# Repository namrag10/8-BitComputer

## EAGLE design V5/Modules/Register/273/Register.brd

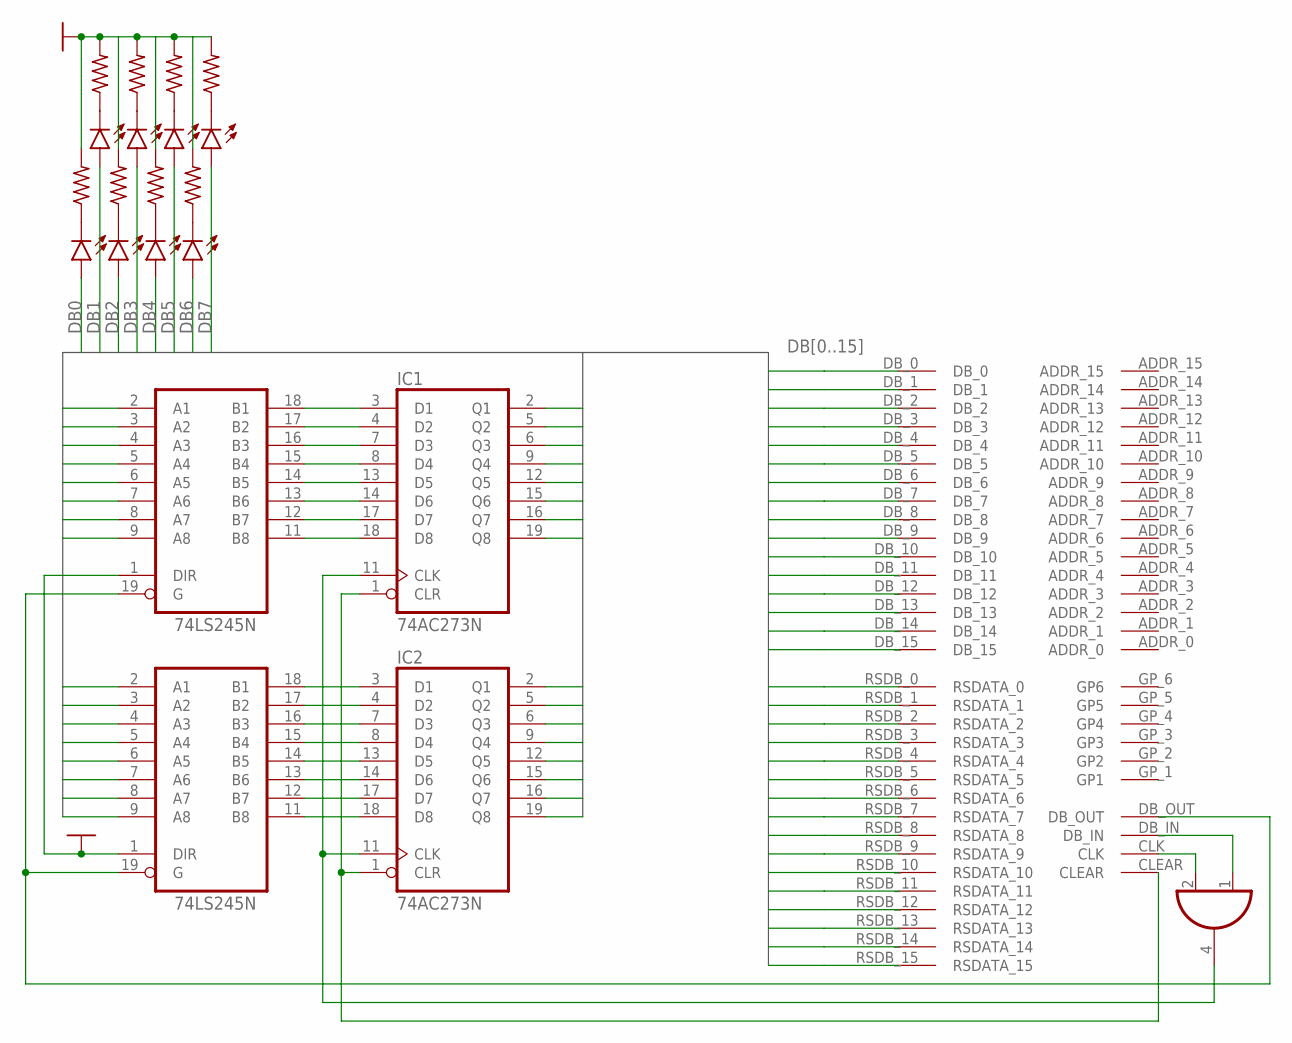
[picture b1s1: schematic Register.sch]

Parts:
IC1, IC2: 74AC273N; DIL20
IC4: 74AHC1G08DCK; SC70-5
LED_A_REG_1, LED_A_REG_2, LED_A_REG_3, LED_A_REG_4, LED_A_REG_5, LED_A_REG_6, LED_A_REG_7, LED_A_REG_8: LED; LED5MM
OUTPUT_BUFFER_REG_A, OUTPUT_BUFFER_REG_A1: 74LS245N; DIL20
R1, R2, R3, R4, R5, R6, R7, R8: ~220; 0204/7
U$1: BACKPLATE_INTERFACE; BACK_INTERFACE-FOOT

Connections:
DB0: IC1.2 (Q1), LED_A_REG_1.A, OUTPUT_BUFFER_REG_A1.2 (A1), U$1.DB_0, U$1.RSDB_0 (RSDATA_0)
DB1: IC1.5 (Q2), LED_A_REG_2.A, OUTPUT_BUFFER_REG_A1.3 (A2), U$1.DB_1, U$1.RSDB_1 (RSDATA_1)
DB2: IC1.6 (Q3), LED_A_REG_3.A, OUTPUT_BUFFER_REG_A1.4 (A3), U$1.DB_2, U$1.RSDB_2 (RSDATA_2)
DB3: IC1.9 (Q4), LED_A_REG_4.A, OUTPUT_BUFFER_REG_A1.5 (A4), U$1.DB_3, U$1.RSDB_3 (RSDATA_3)
DB4: IC1.12 (Q5), LED_A_REG_5.A, OUTPUT_BUFFER_REG_A1.6 (A5), U$1.DB_4, U$1.RSDB_4 (RSDATA_4)
DB5: IC1.15 (Q6), LED_A_REG_6.A, OUTPUT_BUFFER_REG_A1.7 (A6), U$1.DB_5, U$1.RSDB_5 (RSDATA_5)
DB6: IC1.16 (Q7), LED_A_REG_7.A, OUTPUT_BUFFER_REG_A1.8 (A7), U$1.DB_6, U$1.RSDB_6 (RSDATA_6)
DB7: IC1.19 (Q8), LED_A_REG_8.A, OUTPUT_BUFFER_REG_A1.9 (A8), U$1.DB_7, U$1.RSDB_7 (RSDATA_7)
DB8: IC2.2 (Q1), OUTPUT_BUFFER_REG_A.2 (A1), U$1.DB_8, U$1.RSDB_8 (RSDATA_8)
DB9: IC2.5 (Q2), OUTPUT_BUFFER_REG_A.3 (A2), U$1.DB_9, U$1.RSDB_9 (RSDATA_9)
DB10: IC2.6 (Q3), OUTPUT_BUFFER_REG_A.4 (A3), U$1.DB_10, U$1.RSDB_10 (RSDATA_10)
DB11: IC2.9 (Q4), OUTPUT_BUFFER_REG_A.5 (A4), U$1.DB_11, U$1.RSDB_11 (RSDATA_11)
DB12: IC2.12 (Q5), OUTPUT_BUFFER_REG_A.6 (A5), U$1.DB_12, U$1.RSDB_12 (RSDATA_12)
DB13: IC2.15 (Q6), OUTPUT_BUFFER_REG_A.7 (A6), U$1.DB_13, U$1.RSDB_13 (RSDATA_13)
DB14: IC2.16 (Q7), OUTPUT_BUFFER_REG_A.8 (A7), U$1.DB_14, U$1.RSDB_14 (RSDATA_14)
DB15: IC2.19 (Q8), OUTPUT_BUFFER_REG_A.9 (A8), U$1.DB_15, U$1.RSDB_15 (RSDATA_15)
GND: IC1.10 (GND), IC2.10 (GND), IC4.3 (GND), OUTPUT_BUFFER_REG_A.1 (DIR), OUTPUT_BUFFER_REG_A.10 (GND), OUTPUT_BUFFER_REG_A1.1 (DIR), OUTPUT_BUFFER_REG_A1.10 (GND), R1.2, R2.2, R4.2, R6.2, R8.2, U$1.GND, U$1.GND2 (GND)
unnamed: OUTPUT_BUFFER_REG_A.19 (G), OUTPUT_BUFFER_REG_A1.19 (G), U$1.DB_OUT
unnamed: LED_A_REG_1.K (C), R1.1
unnamed: IC1.18 (D8), OUTPUT_BUFFER_REG_A1.11 (B8)
unnamed: IC1.17 (D7), OUTPUT_BUFFER_REG_A1.12 (B7)
unnamed: IC1.14 (D6), OUTPUT_BUFFER_REG_A1.13 (B6)
unnamed: IC1.13 (D5), OUTPUT_BUFFER_REG_A1.14 (B5)
unnamed: IC1.8 (D4), OUTPUT_BUFFER_REG_A1.15 (B4)
unnamed: IC1.7 (D3), OUTPUT_BUFFER_REG_A1.16 (B3)
unnamed: IC1.4 (D2), OUTPUT_BUFFER_REG_A1.17 (B2)
unnamed: IC1.3 (D1), OUTPUT_BUFFER_REG_A1.18 (B1)
unnamed: IC2.18 (D8), OUTPUT_BUFFER_REG_A.11 (B8)
unnamed: IC2.17 (D7), OUTPUT_BUFFER_REG_A.12 (B7)
unnamed: IC2.14 (D6), OUTPUT_BUFFER_REG_A.13 (B6)
unnamed: IC2.13 (D5), OUTPUT_BUFFER_REG_A.14 (B5)
unnamed: IC2.8 (D4), OUTPUT_BUFFER_REG_A.15 (B4)
unnamed: IC2.7 (D3), OUTPUT_BUFFER_REG_A.16 (B3)
unnamed: IC2.4 (D2), OUTPUT_BUFFER_REG_A.17 (B2)
unnamed: IC2.3 (D1), OUTPUT_BUFFER_REG_A.18 (B1)
unnamed: IC4.2 (I1), U$1.CLK
unnamed: IC1.1 (CLR), IC2.1 (CLR), U$1.CLEAR
unnamed: IC1.11 (CLK), IC2.11 (CLK), IC4.4 (O)
unnamed: IC4.1 (I0), U$1.DB_IN
unnamed: LED_A_REG_2.K (C), R2.1
unnamed: LED_A_REG_3.K (C), R3.1
unnamed: LED_A_REG_4.K (C), R4.1
unnamed: LED_A_REG_5.K (C), R5.1
unnamed: LED_A_REG_6.K (C), R6.1
unnamed: LED_A_REG_7.K (C), R7.1
unnamed: LED_A_REG_8.K (C), R8.1
VCC: IC1.20 (VCC), IC2.20 (VCC), IC4.5 (VCC), OUTPUT_BUFFER_REG_A.20 (VCC), OUTPUT_BUFFER_REG_A1.20 (VCC), U$1.VCC, U$1.VCC2 (VCC)

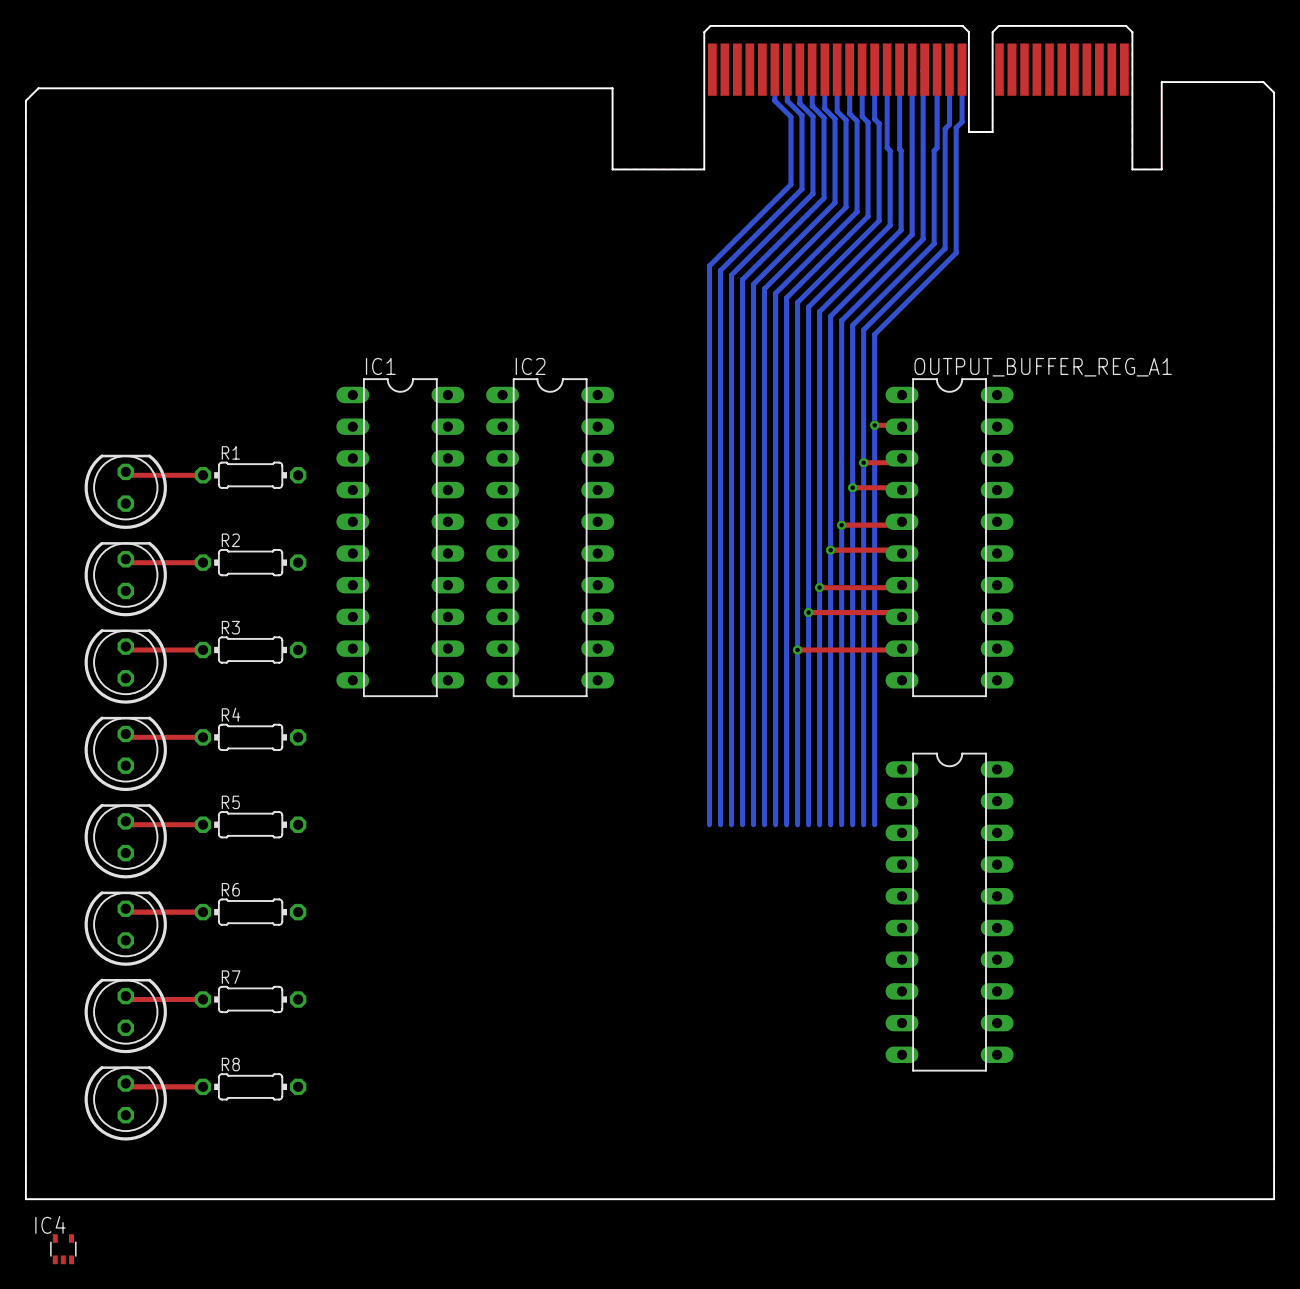
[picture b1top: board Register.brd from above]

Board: 2 copper layers, 100.0 x 94.0 mm, 22 parts (0 on the bottom side), 47 nets.
